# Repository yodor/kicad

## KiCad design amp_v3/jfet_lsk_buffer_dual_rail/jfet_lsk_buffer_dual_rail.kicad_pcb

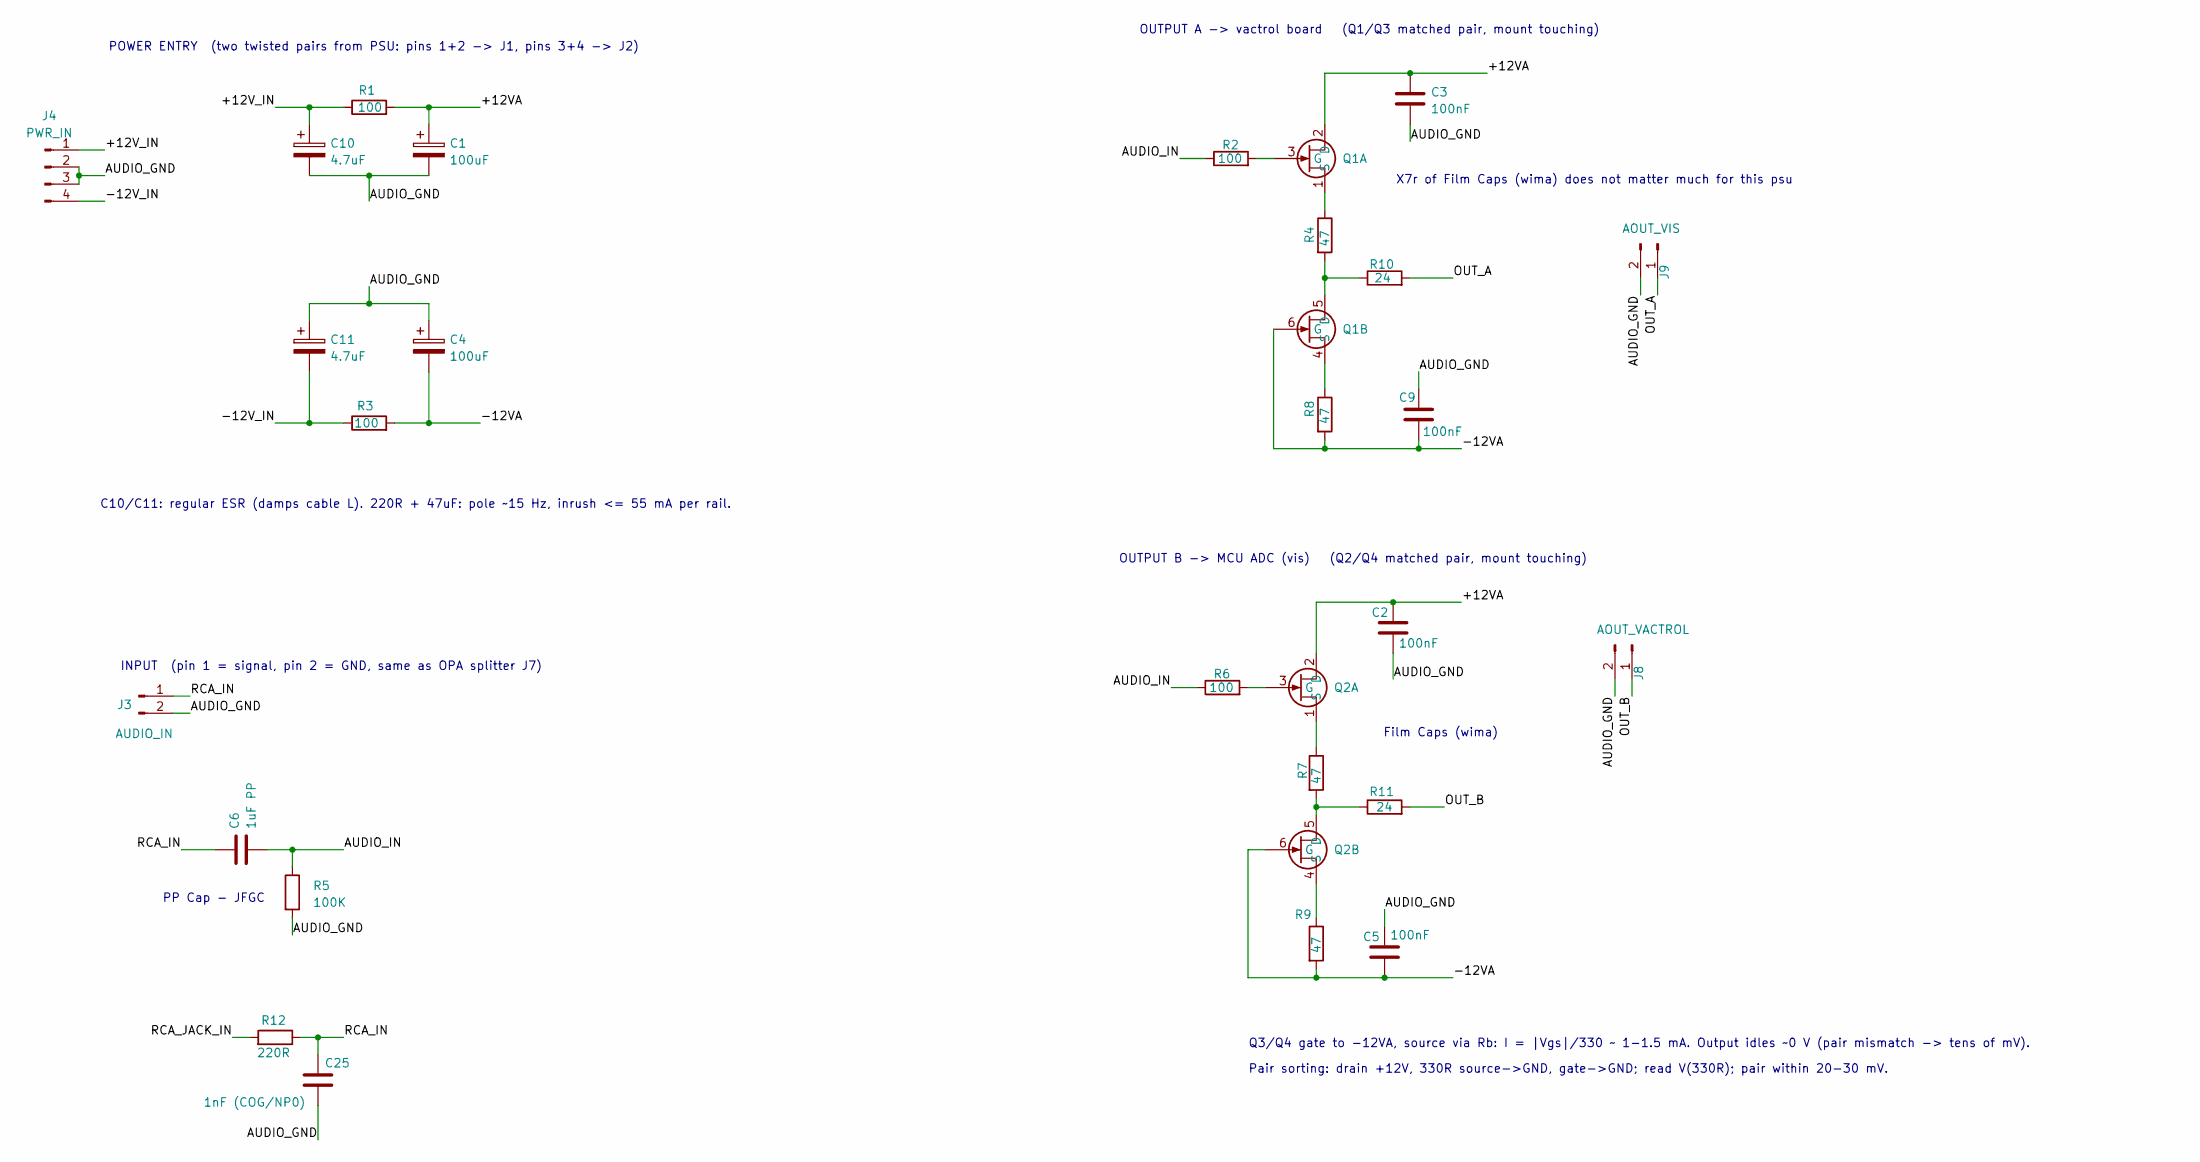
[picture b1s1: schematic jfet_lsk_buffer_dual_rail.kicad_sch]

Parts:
C1, C4: 100uF; CP_Radial_D6.3mm_P2.50mm
C2, C3, C5, C9: 100nF; C_Rect_L4.6mm_W3.0mm_P2.50mm_MKS02_FKP02
C6: 1uF PP; JFC
C10, C11: 4.7uF; CP_Radial_D5.0mm_P2.50mm
C25: 1nF (COG/NP0); C_Disc_D4.3mm_W1.9mm_P5.00mm
J3: AUDIO_IN; JST_XH_B2B-XH-A_1x02_P2.50mm_Vertical
J4: PWR_IN; JST_XH_B4B-XH-A_1x04_P2.50mm_Vertical
J8: AOUT_VACTROL; JST_XH_B2B-XH-A_1x02_P2.50mm_Vertical
J9: AOUT_VIS; JST_XH_B2B-XH-A_1x02_P2.50mm_Vertical
Q1, Q2: TO-75-6
R1, R2, R3, R6: 100; R_Axial_DIN0207_L6.3mm_D2.5mm_P7.62mm_Horizontal
R4, R7: 47; R_Axial_DIN0207_L6.3mm_D2.5mm_P7.62mm_Horizontal
R5: 100K; R_Axial_DIN0207_L6.3mm_D2.5mm_P7.62mm_Horizontal
R8, R9: 47; R_Axial_DIN0207_L6.3mm_D2.5mm_P2.54mm_Vertical
R10, R11: 24; R_Axial_DIN0207_L6.3mm_D2.5mm_P7.62mm_Horizontal
R12: 220R; R_Axial_DIN0207_L6.3mm_D2.5mm_P7.62mm_Horizontal

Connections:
/+12VA: C1.1, C2.1, C3.1, Q1.2 (D), Q2.2 (D), R1.2
/+12V_IN: C10.1, J4.1, R1.1
/-12VA: C4.2, C5.2, C9.2, Q1.6 (G), Q2.6 (G), R3.2, R8.2, R9.2
/-12V_IN: C11.2, J4.4, R3.1
/AUDIO_GND: C1.2, C2.2, C3.2, C4.1, C5.1, C9.1, C10.2, C11.1, C25.1, J3.2, J4.2, J4.3, J8.2, J9.2, R5.2
/AUDIO_IN: C6.2, R2.1, R5.1, R6.1
/OUT_A: J9.1, R10.2
/OUT_B: J8.1, R11.2
/RCA_IN: C6.1, C25.2, J3.1, R12.1
unnamed: Q1.3 (G), R2.2
unnamed: Q1.1 (S), R4.1
unnamed: Q1.5 (D), R4.2, R10.1
unnamed: Q1.4 (S), R8.1
unnamed: Q2.3 (G), R6.2
unnamed: Q2.1 (S), R7.1
unnamed: Q2.5 (D), R7.2, R11.1
unnamed: Q2.4 (S), R9.1

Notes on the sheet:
POWER ENTRY (two twisted pairs from PSU: pins 1+2 -> J1, pins 3+4 -> J2)
OUTPUT B -> MCU ADC (vis) (Q2/Q4 matched pair, mount touching)
PP Cap - JFGC
Pair sorting: drain +12V, 330R source->GND, gate->GND; read V(330R); pair within 20-30 mV.
C10/C11: regular ESR (damps cable L). 220R + 47uF: pole ~15 Hz, inrush <= 55 mA per rail.
INPUT (pin 1 = signal, pin 2 = GND, same as OPA splitter J7)
OUTPUT A -> vactrol board (Q1/Q3 matched pair, mount touching)
Q3/Q4 gate to -12VA, source via Rb: I = |Vgs|/330 ~ 1-1.5 mA. Output idles ~0 V (pair mismatch -> tens of mV).
Film Caps (wima)
X7r of Film Caps (wima) does not matter much for this psu

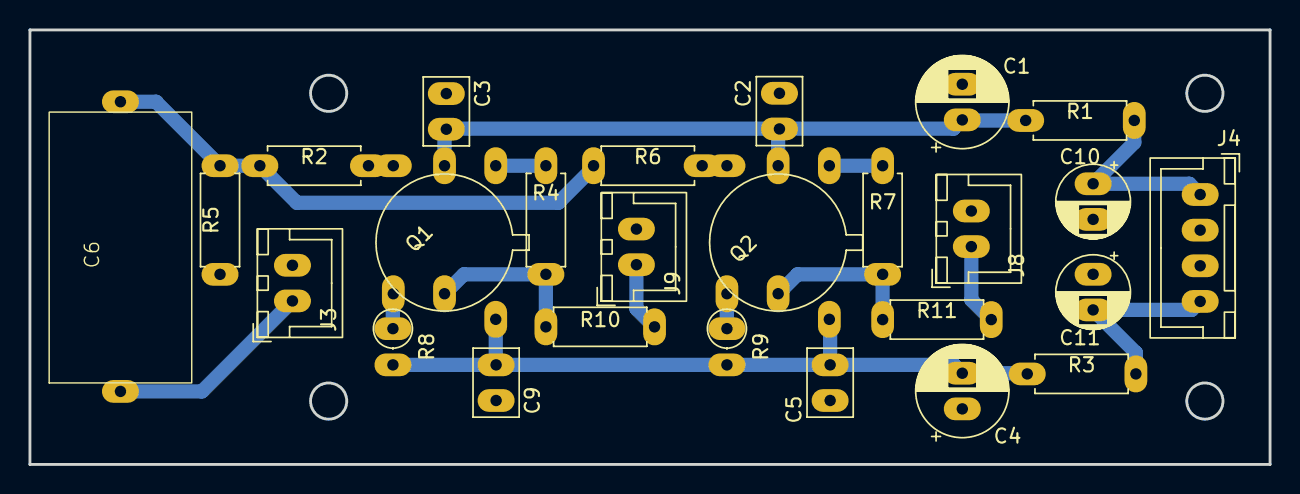
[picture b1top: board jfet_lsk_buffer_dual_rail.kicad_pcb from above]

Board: 2 copper layers, 87.0 x 30.5 mm, 26 parts (0 on the bottom side), 17 nets.

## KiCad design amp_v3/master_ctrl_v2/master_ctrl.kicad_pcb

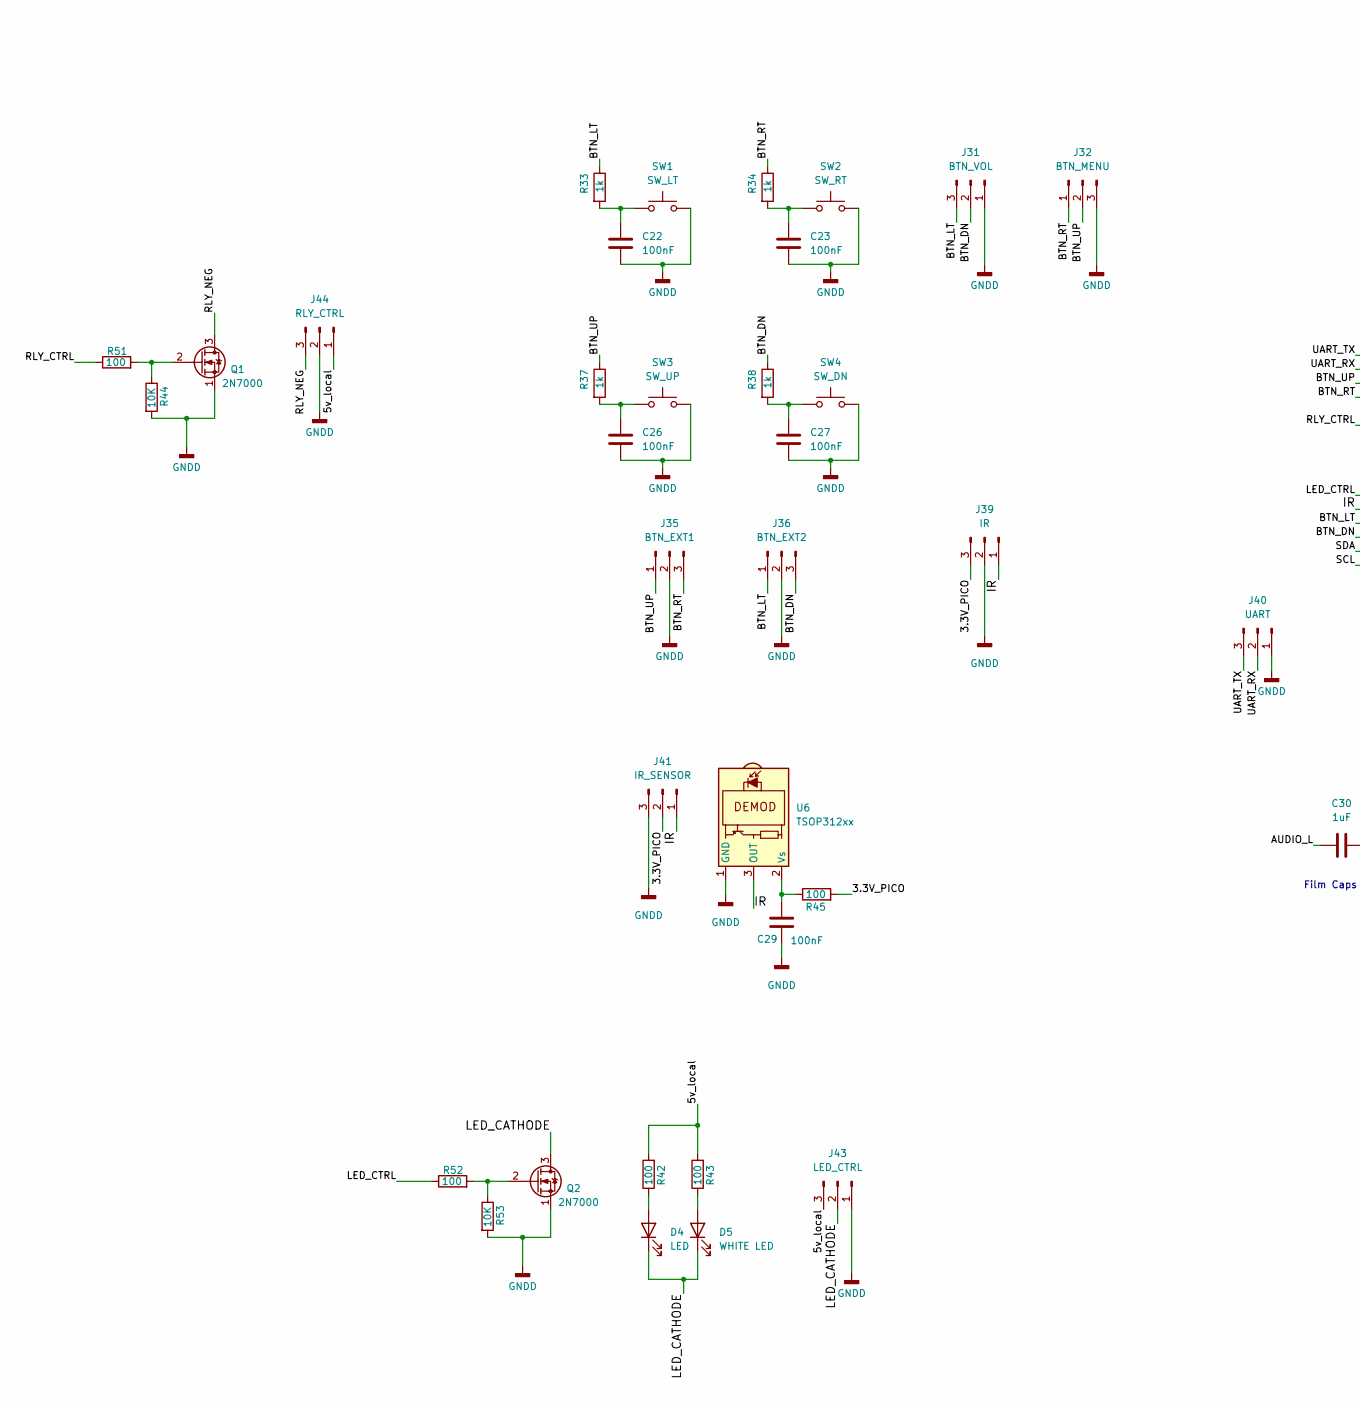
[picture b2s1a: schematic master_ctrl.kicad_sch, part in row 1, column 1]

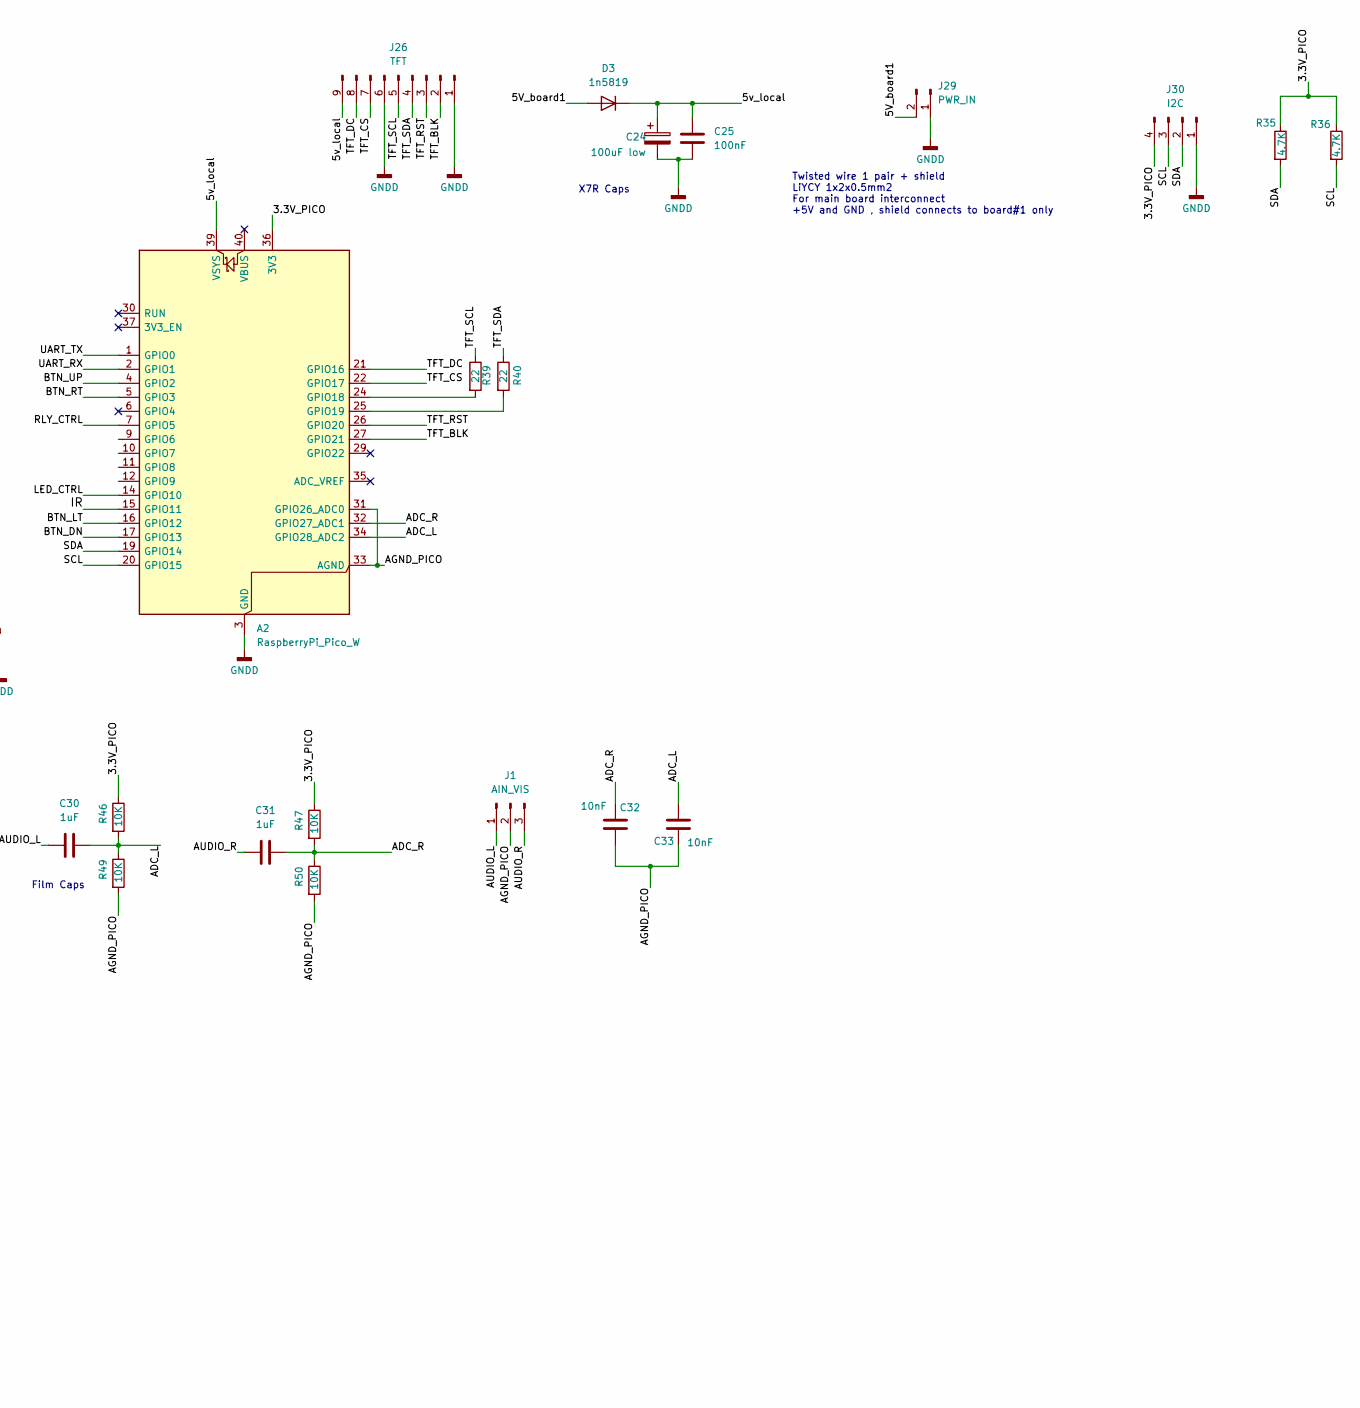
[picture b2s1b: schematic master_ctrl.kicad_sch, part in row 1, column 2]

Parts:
A2: RaspberryPi_Pico_W; RaspberryPi_Pico_Common_THT
C22, C23, C25, C26, C27, C29: 100nF; C_Disc_D5.0mm_W2.5mm_P5.00mm
C24: 100uF low; CP_Radial_D6.3mm_P2.50mm
C30, C31: 1uF; C_Rect_L7.2mm_W5.5mm_P5.00mm_FKS2_FKP2_MKS2_MKP2
C32, C33: 10nF; C_Disc_D5.0mm_W2.5mm_P5.00mm
D3: 1n5819; D_DO-41_SOD81_P3.81mm_Vertical_CathodeUp
D4: LED; LED_D3.0mm_Horizontal_O1.27mm_Z2.0mm
D5: WHITE LED; LED_D3.0mm_Horizontal_O1.27mm_Z2.0mm
J1: AIN_VIS; PinHeader_1x03_P2.54mm_Horizontal
J26: TFT; PinHeader_1x09_P2.54mm_Horizontal
J29: PWR_IN; JST_XH_B2B-XH-A_1x02_P2.50mm_Vertical
J30: I2C; PinHeader_1x04_P2.54mm_Vertical
J31: BTN_VOL; PinHeader_1x03_P2.54mm_Horizontal
J32: BTN_MENU; PinHeader_1x03_P2.54mm_Horizontal
J35: BTN_EXT1; PinHeader_1x03_P2.54mm_Horizontal
J36: BTN_EXT2; PinHeader_1x03_P2.54mm_Horizontal
J39: IR; PinHeader_1x03_P2.54mm_Vertical
J40: UART; JST_XH_B3B-XH-A_1x03_P2.50mm_Vertical
J41: IR_SENSOR; JST_XH_B3B-XH-A_1x03_P2.50mm_Vertical
J43: LED_CTRL; PinHeader_1x03_P2.54mm_Vertical
J44: RLY_CTRL; PinHeader_1x03_P2.54mm_Vertical
Q1, Q2: 2N7000; TO-92_Inline_Wide
R33, R34, R37, R38: 1k; R_Axial_DIN0207_L6.3mm_D2.5mm_P7.62mm_Horizontal
R35, R36: 4.7K; R_Axial_DIN0207_L6.3mm_D2.5mm_P7.62mm_Horizontal
R39, R40: 22; R_Axial_DIN0207_L6.3mm_D2.5mm_P2.54mm_Vertical
R42, R43, R45: 100; R_Axial_DIN0207_L6.3mm_D2.5mm_P2.54mm_Vertical
R44, R53: 10K; R_Axial_DIN0207_L6.3mm_D2.5mm_P7.62mm_Horizontal
R46, R47, R49, R50: 10K; R_Axial_DIN0207_L6.3mm_D2.5mm_P2.54mm_Vertical
R51, R52: 100; R_Axial_DIN0207_L6.3mm_D2.5mm_P7.62mm_Horizontal
SW1: SW_LT; SW_SPST_Omron_B3F-50xx
SW2: SW_RT; SW_SPST_Omron_B3F-50xx
SW3: SW_UP; SW_SPST_Omron_B3F-50xx
SW4: SW_DN; SW_SPST_Omron_B3F-50xx
U6: TSOP312xx; Vishay_CAST-3Pin

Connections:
/3.3V_PICO: A2.36 (3V3), J30.4, J39.3, J41.2, R35.1, R36.1, R45.2, R46.1, R47.1
/5V_board1: D3.2 (A), J29.2
/5v_local: A2.39 (VSYS), C24.1, C25.1, D3.1 (K), J26.9, J43.3, J44.1, R42.2, R43.2
/ADC_L: A2.34 (GPIO28_ADC2), C30.2, C33.1, R46.2, R49.1
/ADC_R: A2.32 (GPIO27_ADC1), C31.2, C32.2, R47.2, R50.1
/AGND_PICO: A2.31 (GPIO26_ADC0), A2.33 (AGND), C32.1, C33.2, J1.2, R49.2, R50.2
/AUDIO_L: C30.1, J1.1
/AUDIO_R: C31.1, J1.3
/BTN_DN: A2.17 (GPIO13), J31.2, J36.3, R38.1
/BTN_LT: A2.16 (GPIO12), J31.3, J36.1, R33.1
/BTN_RT: A2.5 (GPIO3), J32.1, J35.3, R34.1
/BTN_UP: A2.4 (GPIO2), J32.2, J35.1, R37.1
/IR: A2.15 (GPIO11), J39.1, J41.1, U6.3 (OUT)
/LED_CATHODE: D4.1 (K), D5.1 (K), J43.2, Q2.3 (D)
/LED_CTRL: A2.14 (GPIO10), R52.1
/RLY_CTRL: A2.7 (GPIO5), R51.1
/RLY_NEG: J44.3, Q1.3 (D)
/SCL: A2.20 (GPIO15), J30.3, R36.2
/SDA: A2.19 (GPIO14), J30.2, R35.2
/TFT_BLK: A2.27 (GPIO21), J26.2
/TFT_CS: A2.22 (GPIO17), J26.7
/TFT_DC: A2.21 (GPIO16), J26.8
/TFT_RST: A2.26 (GPIO20), J26.3
/TFT_SCL: J26.5, R39.1
/TFT_SDA: J26.4, R40.1
/UART_RX: A2.2 (GPIO1), J40.2
/UART_TX: A2.1 (GPIO0), J40.3
GNDD: A2.3 (GND), A2.8 (GND), A2.13 (GND), A2.18 (GND), A2.23 (GND), A2.28 (GND), A2.38 (GND), C22.2, C23.2, C24.2, C25.2, C26.2, C27.2, C29.2, J26.1, J26.6, J29.1, J30.1, J31.1, J32.3, J35.2, J36.2, J39.2, J40.1, J41.3, J43.1, J44.2, Q1.1 (S), Q2.1 (S), R44.2, R53.2, SW1.2, SW2.2, SW3.2, SW4.2, U6.1 (GND)
unnamed: A2.24 (GPIO18), R39.2
unnamed: A2.25 (GPIO19), R40.2
unnamed: C22.1, R33.2, SW1.1
unnamed: C23.1, R34.2, SW2.1
unnamed: C26.1, R37.2, SW3.1
unnamed: C27.1, R38.2, SW4.1
unnamed: D4.2 (A), R42.1
unnamed: D5.2 (A), R43.1
unnamed: Q1.2 (G), R44.1, R51.2
unnamed: Q2.2 (G), R52.2, R53.1
unnamed: C29.1, R45.1, U6.2 (Vs)

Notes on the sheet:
Twisted wire 1 pair + shield LiYCY 1x2x0.5mm2 For main board interconnect +5V and GND , shield connects to board#1 only
X7R Caps
Film Caps

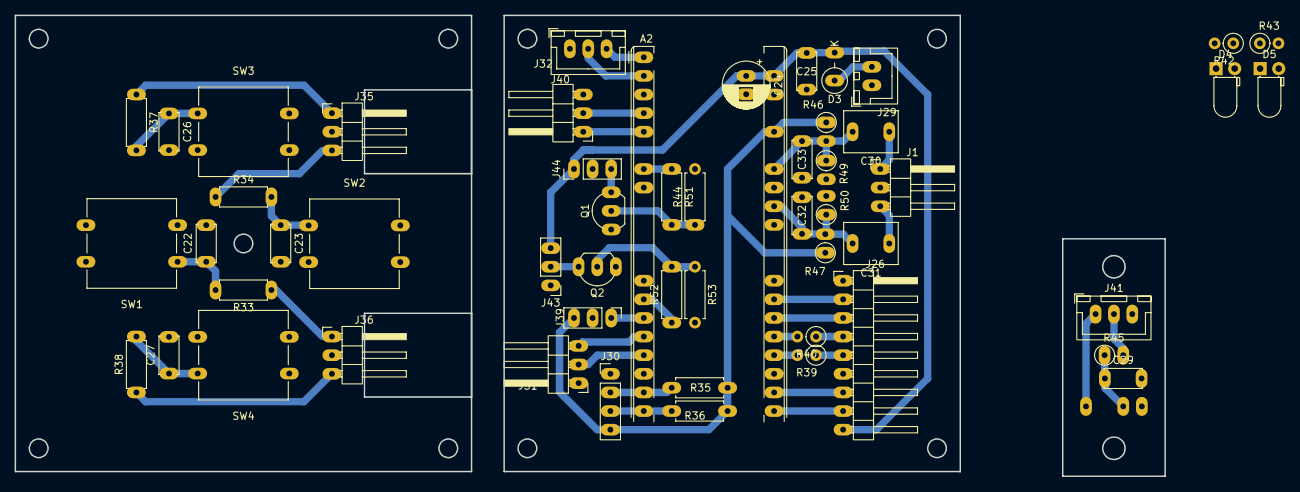
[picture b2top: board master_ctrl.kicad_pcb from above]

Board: 2 copper layers, 156.8 x 62.9 mm, 54 parts (1 on the bottom side), 39 nets.

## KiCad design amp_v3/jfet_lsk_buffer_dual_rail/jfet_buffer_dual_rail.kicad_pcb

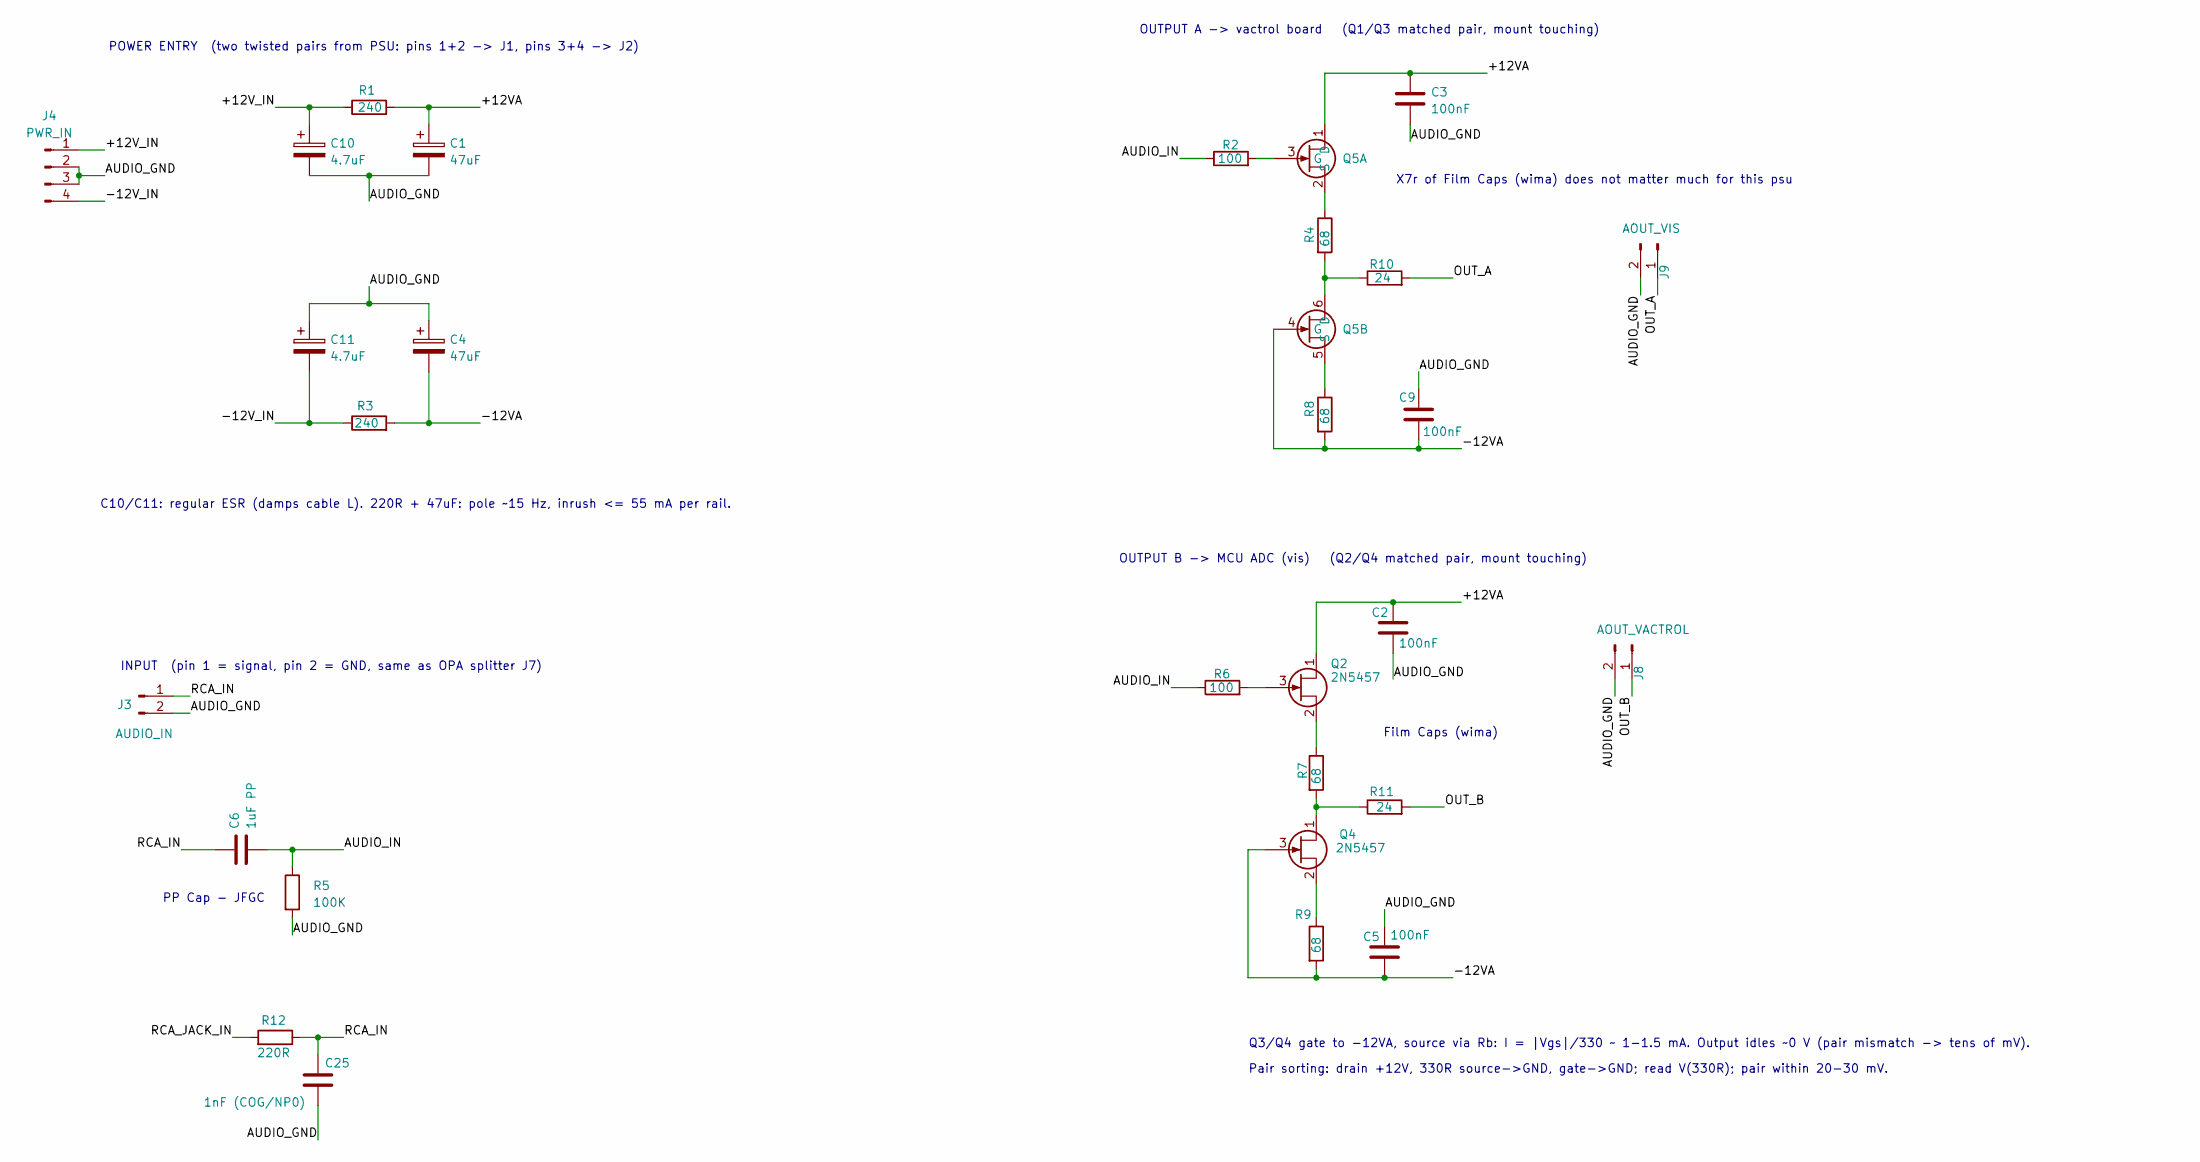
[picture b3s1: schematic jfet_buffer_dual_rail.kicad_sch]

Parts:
C1, C4: 47uF; CP_Radial_D6.3mm_P2.50mm
C2, C3, C5, C9: 100nF; C_Rect_L4.6mm_W3.0mm_P2.50mm_MKS02_FKP02
C6: 1uF PP; JFC
C10, C11: 4.7uF; CP_Radial_D5.0mm_P2.50mm
C25: 1nF (COG/NP0); C_Disc_D4.3mm_W1.9mm_P5.00mm
J3: AUDIO_IN; JST_XH_B2B-XH-A_1x02_P2.50mm_Vertical
J4: PWR_IN; JST_XH_B4B-XH-A_1x04_P2.50mm_Vertical
J8: AOUT_VACTROL; JST_XH_B2B-XH-A_1x02_P2.50mm_Vertical
J9: AOUT_VIS; JST_XH_B2B-XH-A_1x02_P2.50mm_Vertical
Q2, Q4: 2N5457; TO-92L_Inline_Wide
Q5: TO-75-6
R1, R3: 240; R_Axial_DIN0207_L6.3mm_D2.5mm_P7.62mm_Horizontal
R2, R6: 100; R_Axial_DIN0207_L6.3mm_D2.5mm_P7.62mm_Horizontal
R4, R7, R8, R9: 68; R_Axial_DIN0207_L6.3mm_D2.5mm_P7.62mm_Horizontal
R5: 100K; R_Axial_DIN0207_L6.3mm_D2.5mm_P2.54mm_Vertical
R10, R11: 24; R_Axial_DIN0207_L6.3mm_D2.5mm_P7.62mm_Horizontal
R12: 220R; R_Axial_DIN0207_L6.3mm_D2.5mm_P7.62mm_Horizontal

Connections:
/+12VA: C1.1, C2.1, C3.1, Q2.1 (D), Q5.1 (D), R1.2
/+12V_IN: C10.1, J4.1, R1.1
/-12VA: C4.2, C5.2, C9.2, Q4.3 (G), Q5.4 (G), R3.2, R8.2, R9.2
/-12V_IN: C11.2, J4.4, R3.1
/AUDIO_GND: C1.2, C2.2, C3.2, C4.1, C5.1, C9.1, C10.2, C11.1, C25.1, J3.2, J4.2, J4.3, J8.2, J9.2, R5.2
/AUDIO_IN: C6.2, R2.1, R5.1, R6.1
/OUT_A: J9.1, R10.2
/OUT_B: J8.1, R11.2
/RCA_IN: C6.1, C25.2, J3.1, R12.1
/RCA_JACK_IN: R12.2
unnamed: Q2.3 (G), R6.2
unnamed: Q2.2 (S), R7.1
unnamed: Q4.1 (D), R7.2, R11.1
unnamed: Q4.2 (S), R9.1
unnamed: Q5.3 (G), R2.2
unnamed: Q5.2 (S), R4.1
unnamed: Q5.6 (D), R4.2, R10.1
unnamed: Q5.5 (S), R8.1

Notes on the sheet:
POWER ENTRY (two twisted pairs from PSU: pins 1+2 -> J1, pins 3+4 -> J2)
OUTPUT B -> MCU ADC (vis) (Q2/Q4 matched pair, mount touching)
PP Cap - JFGC
Pair sorting: drain +12V, 330R source->GND, gate->GND; read V(330R); pair within 20-30 mV.
C10/C11: regular ESR (damps cable L). 220R + 47uF: pole ~15 Hz, inrush <= 55 mA per rail.
INPUT (pin 1 = signal, pin 2 = GND, same as OPA splitter J7)
OUTPUT A -> vactrol board (Q1/Q3 matched pair, mount touching)
Q3/Q4 gate to -12VA, source via Rb: I = |Vgs|/330 ~ 1-1.5 mA. Output idles ~0 V (pair mismatch -> tens of mV).
Film Caps (wima)
X7r of Film Caps (wima) does not matter much for this psu

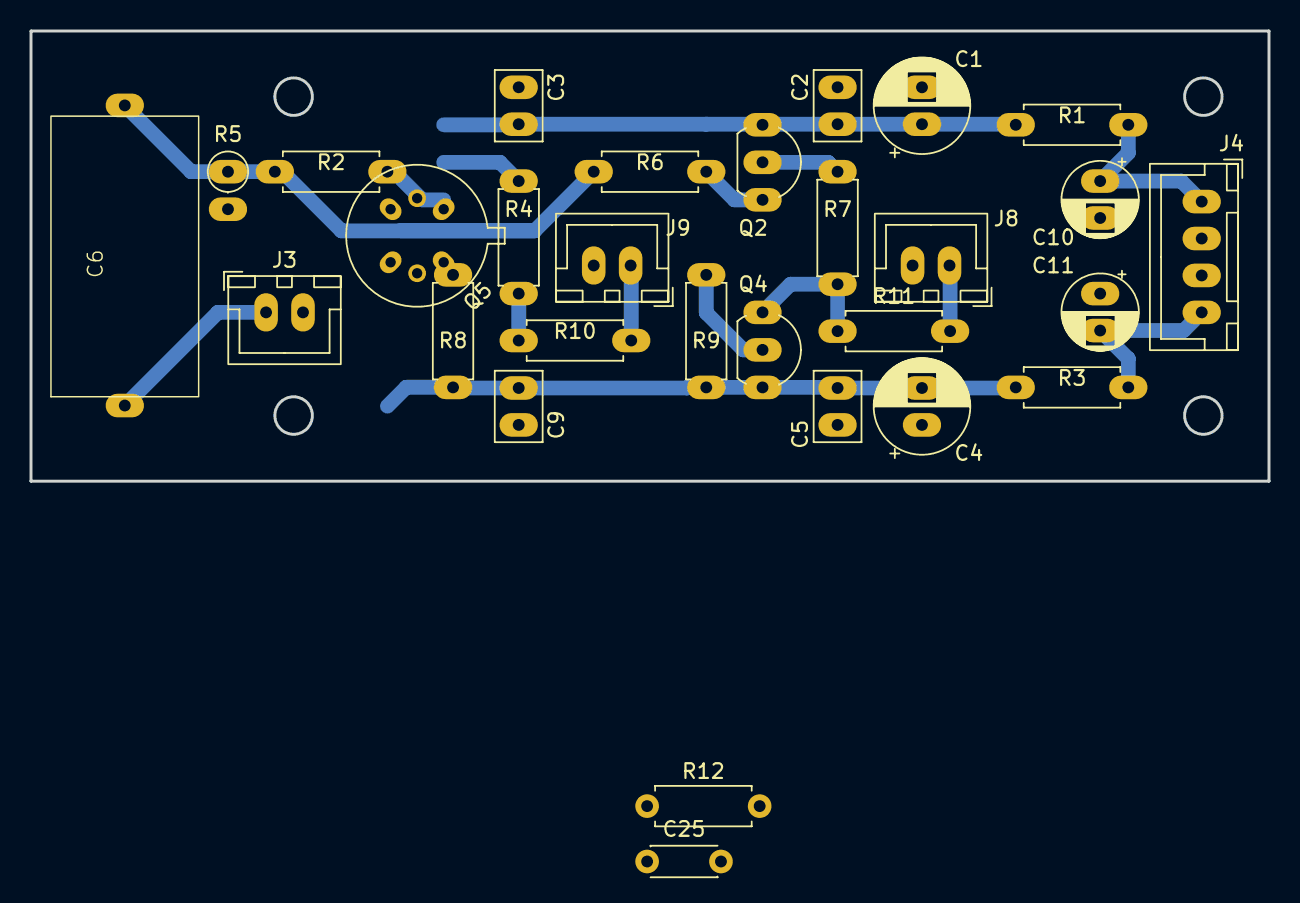
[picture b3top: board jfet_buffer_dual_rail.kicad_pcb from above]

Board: 2 copper layers, 83.8 x 30.5 mm, 29 parts (0 on the bottom side), 17 nets.

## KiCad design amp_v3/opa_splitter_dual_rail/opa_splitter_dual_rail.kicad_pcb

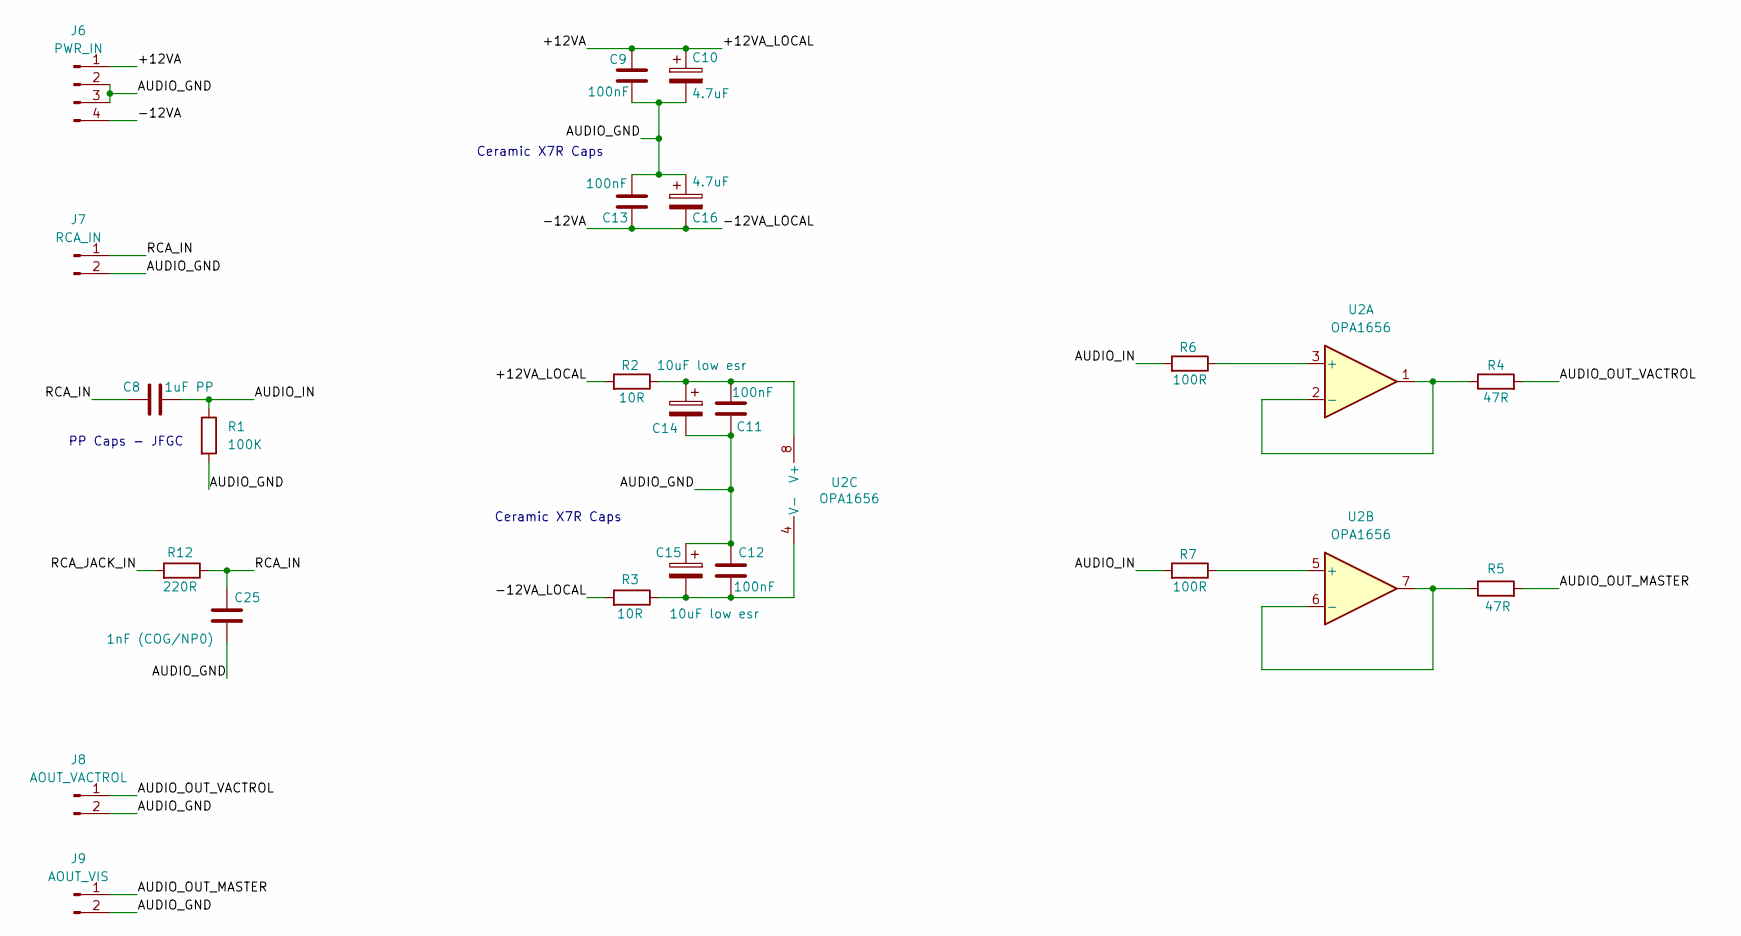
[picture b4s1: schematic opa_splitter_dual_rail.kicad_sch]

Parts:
C8: 1uF PP; JFC
C9, C11, C13: 100nF; C_Disc_D3.8mm_W2.6mm_P2.50mm
C10, C16: 4.7uF; CP_Radial_D5.0mm_P2.50mm
C12: 100nF; C_Disc_D4.3mm_W1.9mm_P5.00mm
C14, C15: 10uF low esr; CP_Radial_D5.0mm_P2.50mm
C25: 1nF (COG/NP0); C_Disc_D4.3mm_W1.9mm_P5.00mm
J6: PWR_IN; JST_XH_B4B-XH-A_1x04_P2.50mm_Vertical
J7: RCA_IN; JST_XH_B2B-XH-A_1x02_P2.50mm_Vertical
J8: AOUT_VACTROL; JST_XH_B2B-XH-A_1x02_P2.50mm_Vertical
J9: AOUT_VIS; JST_XH_B2B-XH-A_1x02_P2.50mm_Vertical
R1: 100K; R_Axial_DIN0207_L6.3mm_D2.5mm_P2.54mm_Vertical
R2, R3: 10R; R_Axial_DIN0207_L6.3mm_D2.5mm_P7.62mm_Horizontal
R4, R5: 47R; R_Axial_DIN0207_L6.3mm_D2.5mm_P2.54mm_Vertical
R6, R7: 100R; R_Axial_DIN0207_L6.3mm_D2.5mm_P7.62mm_Horizontal
R12: 220R; R_Axial_DIN0207_L6.3mm_D2.5mm_P7.62mm_Horizontal
U2: OPA1656; SMDIP-8_W7.62mm

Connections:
/+12VA: C9.2, C10.1, J6.1, R2.2
/-12VA: C13.1, C16.2, J6.4, R3.2
/AUDIO_GND: C9.1, C10.2, C11.1, C12.2, C13.2, C14.2, C15.1, C16.1, C25.1, J6.2, J6.3, J7.2, J8.2, J9.2, R1.2
/AUDIO_IN: C8.2, R1.1, R6.2, R7.2
/AUDIO_OUT_MASTER: J9.1, R5.2
/AUDIO_OUT_VACTROL: J8.1, R4.2
/RCA_IN: C8.1, C25.2, J7.1, R12.1
unnamed: R6.1, U2.3 (+)
unnamed: R4.1, U2.1, U2.2 (-)
unnamed: R7.1, U2.5 (+)
unnamed: R5.1, U2.6 (-), U2.7
unnamed: C11.2, C14.1, R2.1, U2.8 (V+)
unnamed: C12.1, C15.2, R3.1, U2.4 (V-)

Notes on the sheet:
Ceramic X7R Caps
PP Caps - JFGC

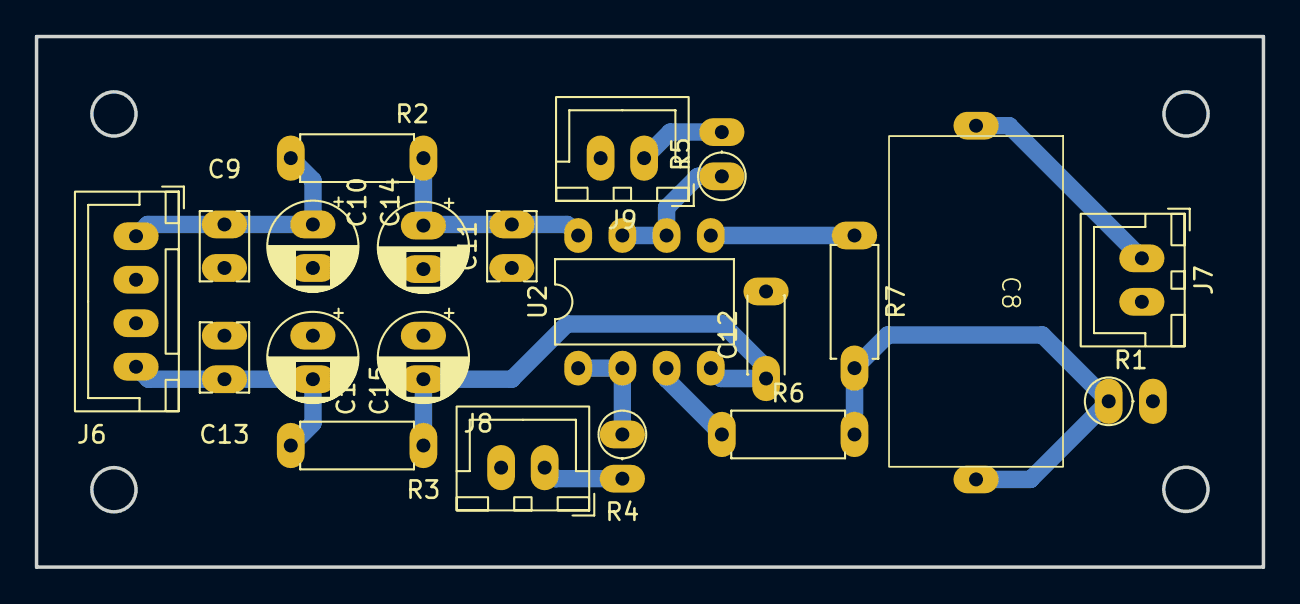
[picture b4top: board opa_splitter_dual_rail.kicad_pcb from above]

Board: 2 copper layers, 70.5 x 30.5 mm, 21 parts (0 on the bottom side), 13 nets.

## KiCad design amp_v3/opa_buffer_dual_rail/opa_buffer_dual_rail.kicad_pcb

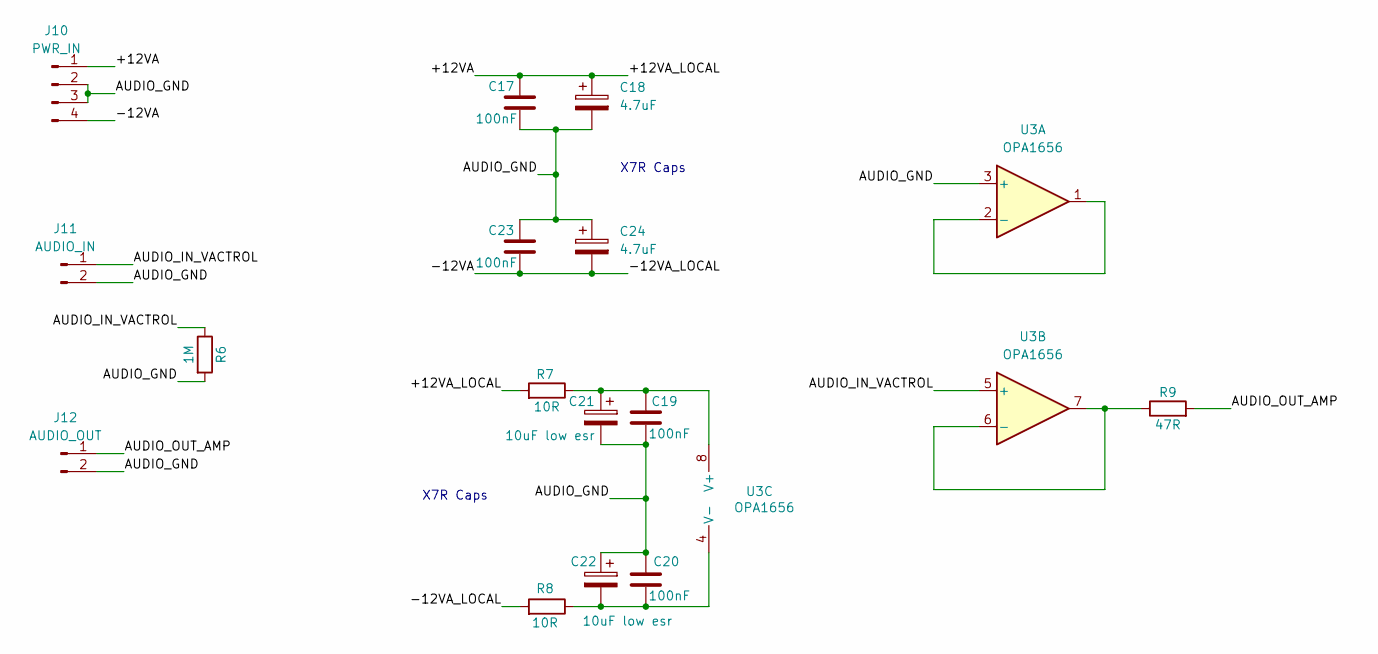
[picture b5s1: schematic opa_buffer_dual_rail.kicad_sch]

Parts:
C17, C19, C20, C23: 100nF; C_Disc_D3.8mm_W2.6mm_P2.50mm
C18, C24: 4.7uF; CP_Radial_D5.0mm_P2.50mm
C21, C22: 10uF low esr; CP_Radial_D5.0mm_P2.50mm
J10: PWR_IN; JST_XH_B4B-XH-A_1x04_P2.50mm_Vertical
J11: AUDIO_IN; JST_XH_B2B-XH-A_1x02_P2.50mm_Vertical
J12: AUDIO_OUT; JST_XH_B2B-XH-A_1x02_P2.50mm_Vertical
R6: 1M; R_Axial_DIN0207_L6.3mm_D2.5mm_P7.62mm_Horizontal
R7, R8: 10R; R_Axial_DIN0207_L6.3mm_D2.5mm_P7.62mm_Horizontal
R9: 47R; R_Axial_DIN0207_L6.3mm_D2.5mm_P2.54mm_Vertical
U3: OPA1656; SMDIP-8_W7.62mm

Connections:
/+12VA: C17.2, C18.1, J10.1, R7.2
/-12VA: C23.1, C24.2, J10.4, R8.2
/AUDIO_GND: C17.1, C18.2, C19.1, C20.2, C21.2, C22.1, C23.2, C24.1, J10.2, J10.3, J11.2, J12.2, R6.2, U3.3 (+)
/AUDIO_IN_VACTROL: J11.1, R6.1, U3.5 (+)
/AUDIO_OUT_AMP: J12.1, R9.2
unnamed: U3.1, U3.2 (-)
unnamed: R9.1, U3.6 (-), U3.7
unnamed: C19.2, C21.1, R7.1, U3.8 (V+)
unnamed: C20.1, C22.2, R8.1, U3.4 (V-)

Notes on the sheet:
X7R Caps

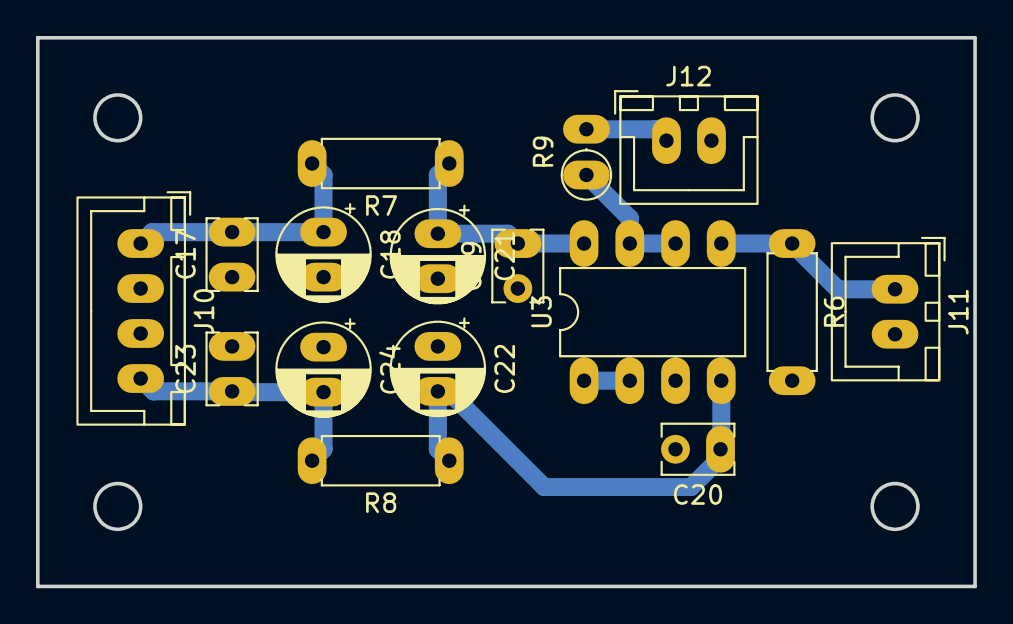
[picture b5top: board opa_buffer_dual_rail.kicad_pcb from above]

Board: 2 copper layers, 52.1 x 30.5 mm, 16 parts (0 on the bottom side), 9 nets.

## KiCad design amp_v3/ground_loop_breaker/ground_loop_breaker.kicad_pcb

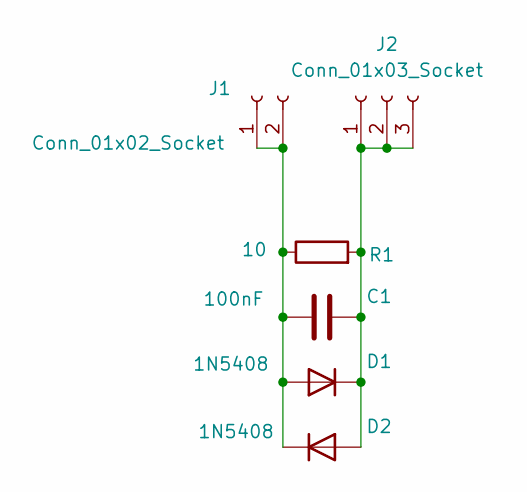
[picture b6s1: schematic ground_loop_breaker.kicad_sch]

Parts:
C1: 100nF; C_Rect_L16.5mm_W6.0mm_P15.00mm_MKT
D1: 1N5408; D_DO-201AD_P5.08mm_Vertical_CathodeUp
D2: 1N5408; D_DO-201AD_P5.08mm_Vertical_AnodeUp
J1: Conn_01x02_Socket; TerminalBlock_Phoenix_PT-1,5-2-5.0-H_1x02_P5.00mm_Horizontal
J2: Conn_01x03_Socket; TerminalBlock_Phoenix_PT-1,5-3-5.0-H_1x03_P5.00mm_Horizontal
R1: 10; R_Axial_Power_L25.0mm_W6.4mm_P27.94mm

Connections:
unnamed: C1.1, D1.2 (A), D2.1 (K), J1.1, J1.2, R1.1
unnamed: C1.2, D1.1 (K), D2.2 (A), J2.1, J2.2, J2.3, R1.2

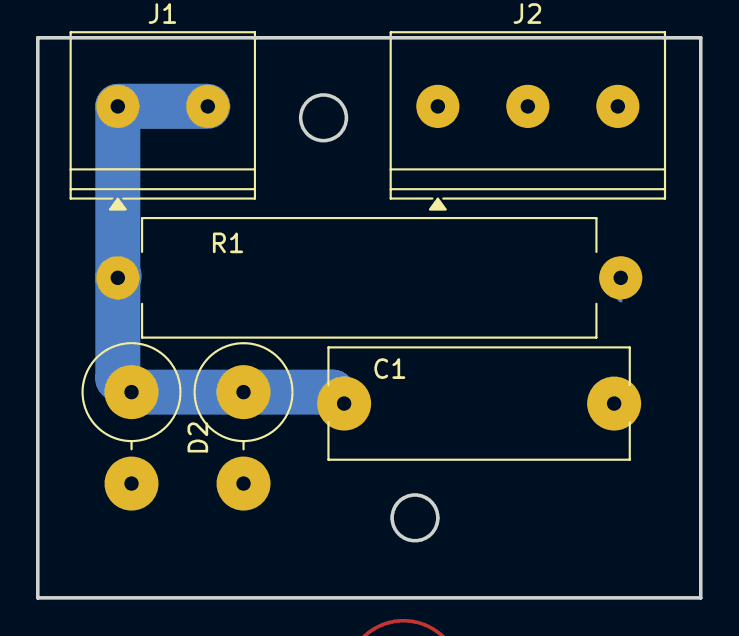
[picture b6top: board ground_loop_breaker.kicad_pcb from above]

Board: 2 copper layers, 36.8 x 31.1 mm, 6 parts (0 on the bottom side), 2 nets.
